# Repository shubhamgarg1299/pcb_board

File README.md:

# pcb_board

Getting started with pcb designing using eagle

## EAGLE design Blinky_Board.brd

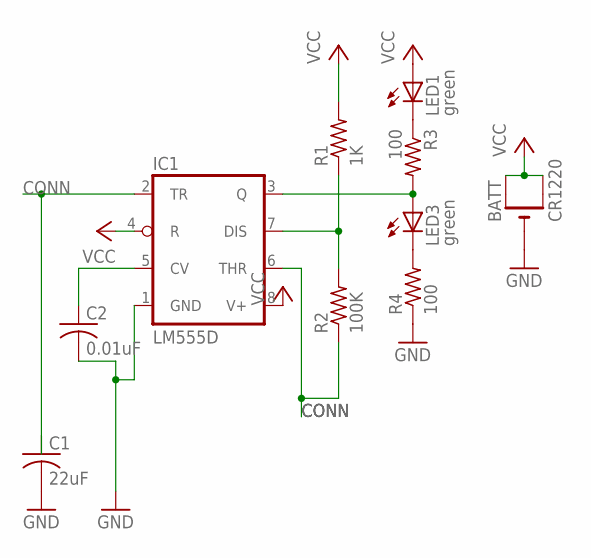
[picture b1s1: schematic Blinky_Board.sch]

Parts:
BATT: CR1220; CR1220-SMD
C1: 22uF; C0805
C2: 0.01uF; C0805
IC1: LM555D; SO08
LED1, LED3: green; CHIPLED_0805
R1: 1K; R0805
R2: 100K; R0805
R3, R4: 100; R0805

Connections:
CONN: C1.1, IC1.2 (TR), IC1.6 (THR), R2.1
GND: BATT.-, C1.2, R4.1
unnamed: LED1.C, R3.1
unnamed: IC1.3 (Q), LED3.A, R3.2
unnamed: LED3.C, R4.2
unnamed: IC1.7 (DIS), R1.1, R2.2
unnamed: C2.2, IC1.1 (GND)
unnamed: C2.1, IC1.5 (CV)
VCC: BATT.+$1 (+), BATT.+$2 (+1), IC1.4 (R), IC1.8 (V+), LED1.A, R1.2

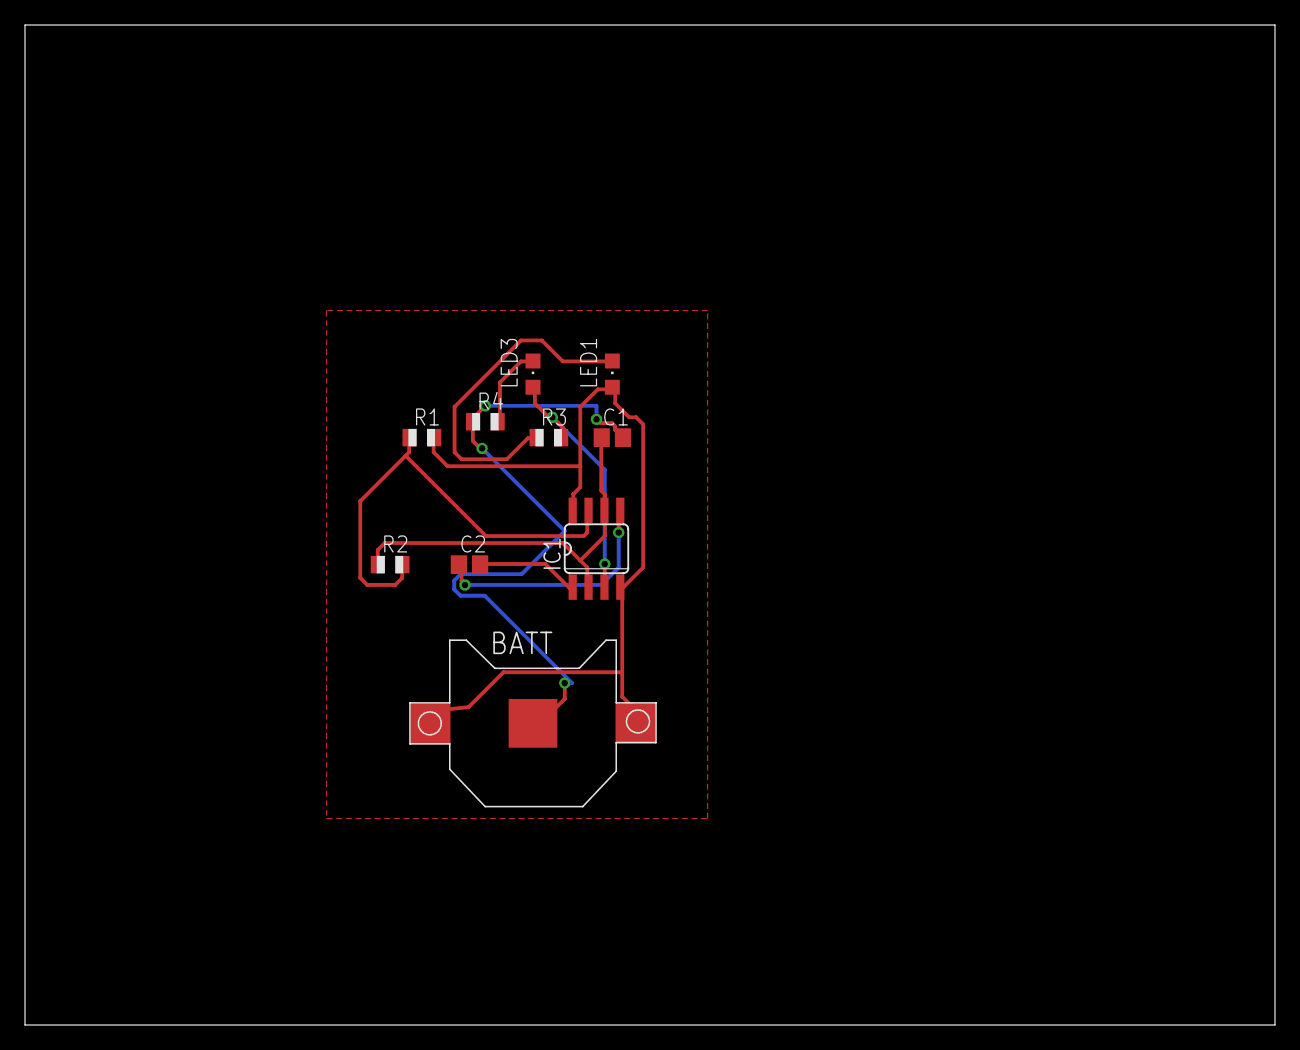
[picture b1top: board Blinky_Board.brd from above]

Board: 2 copper layers, 100.0 x 80.0 mm, 10 parts (0 on the bottom side), 9 nets.
